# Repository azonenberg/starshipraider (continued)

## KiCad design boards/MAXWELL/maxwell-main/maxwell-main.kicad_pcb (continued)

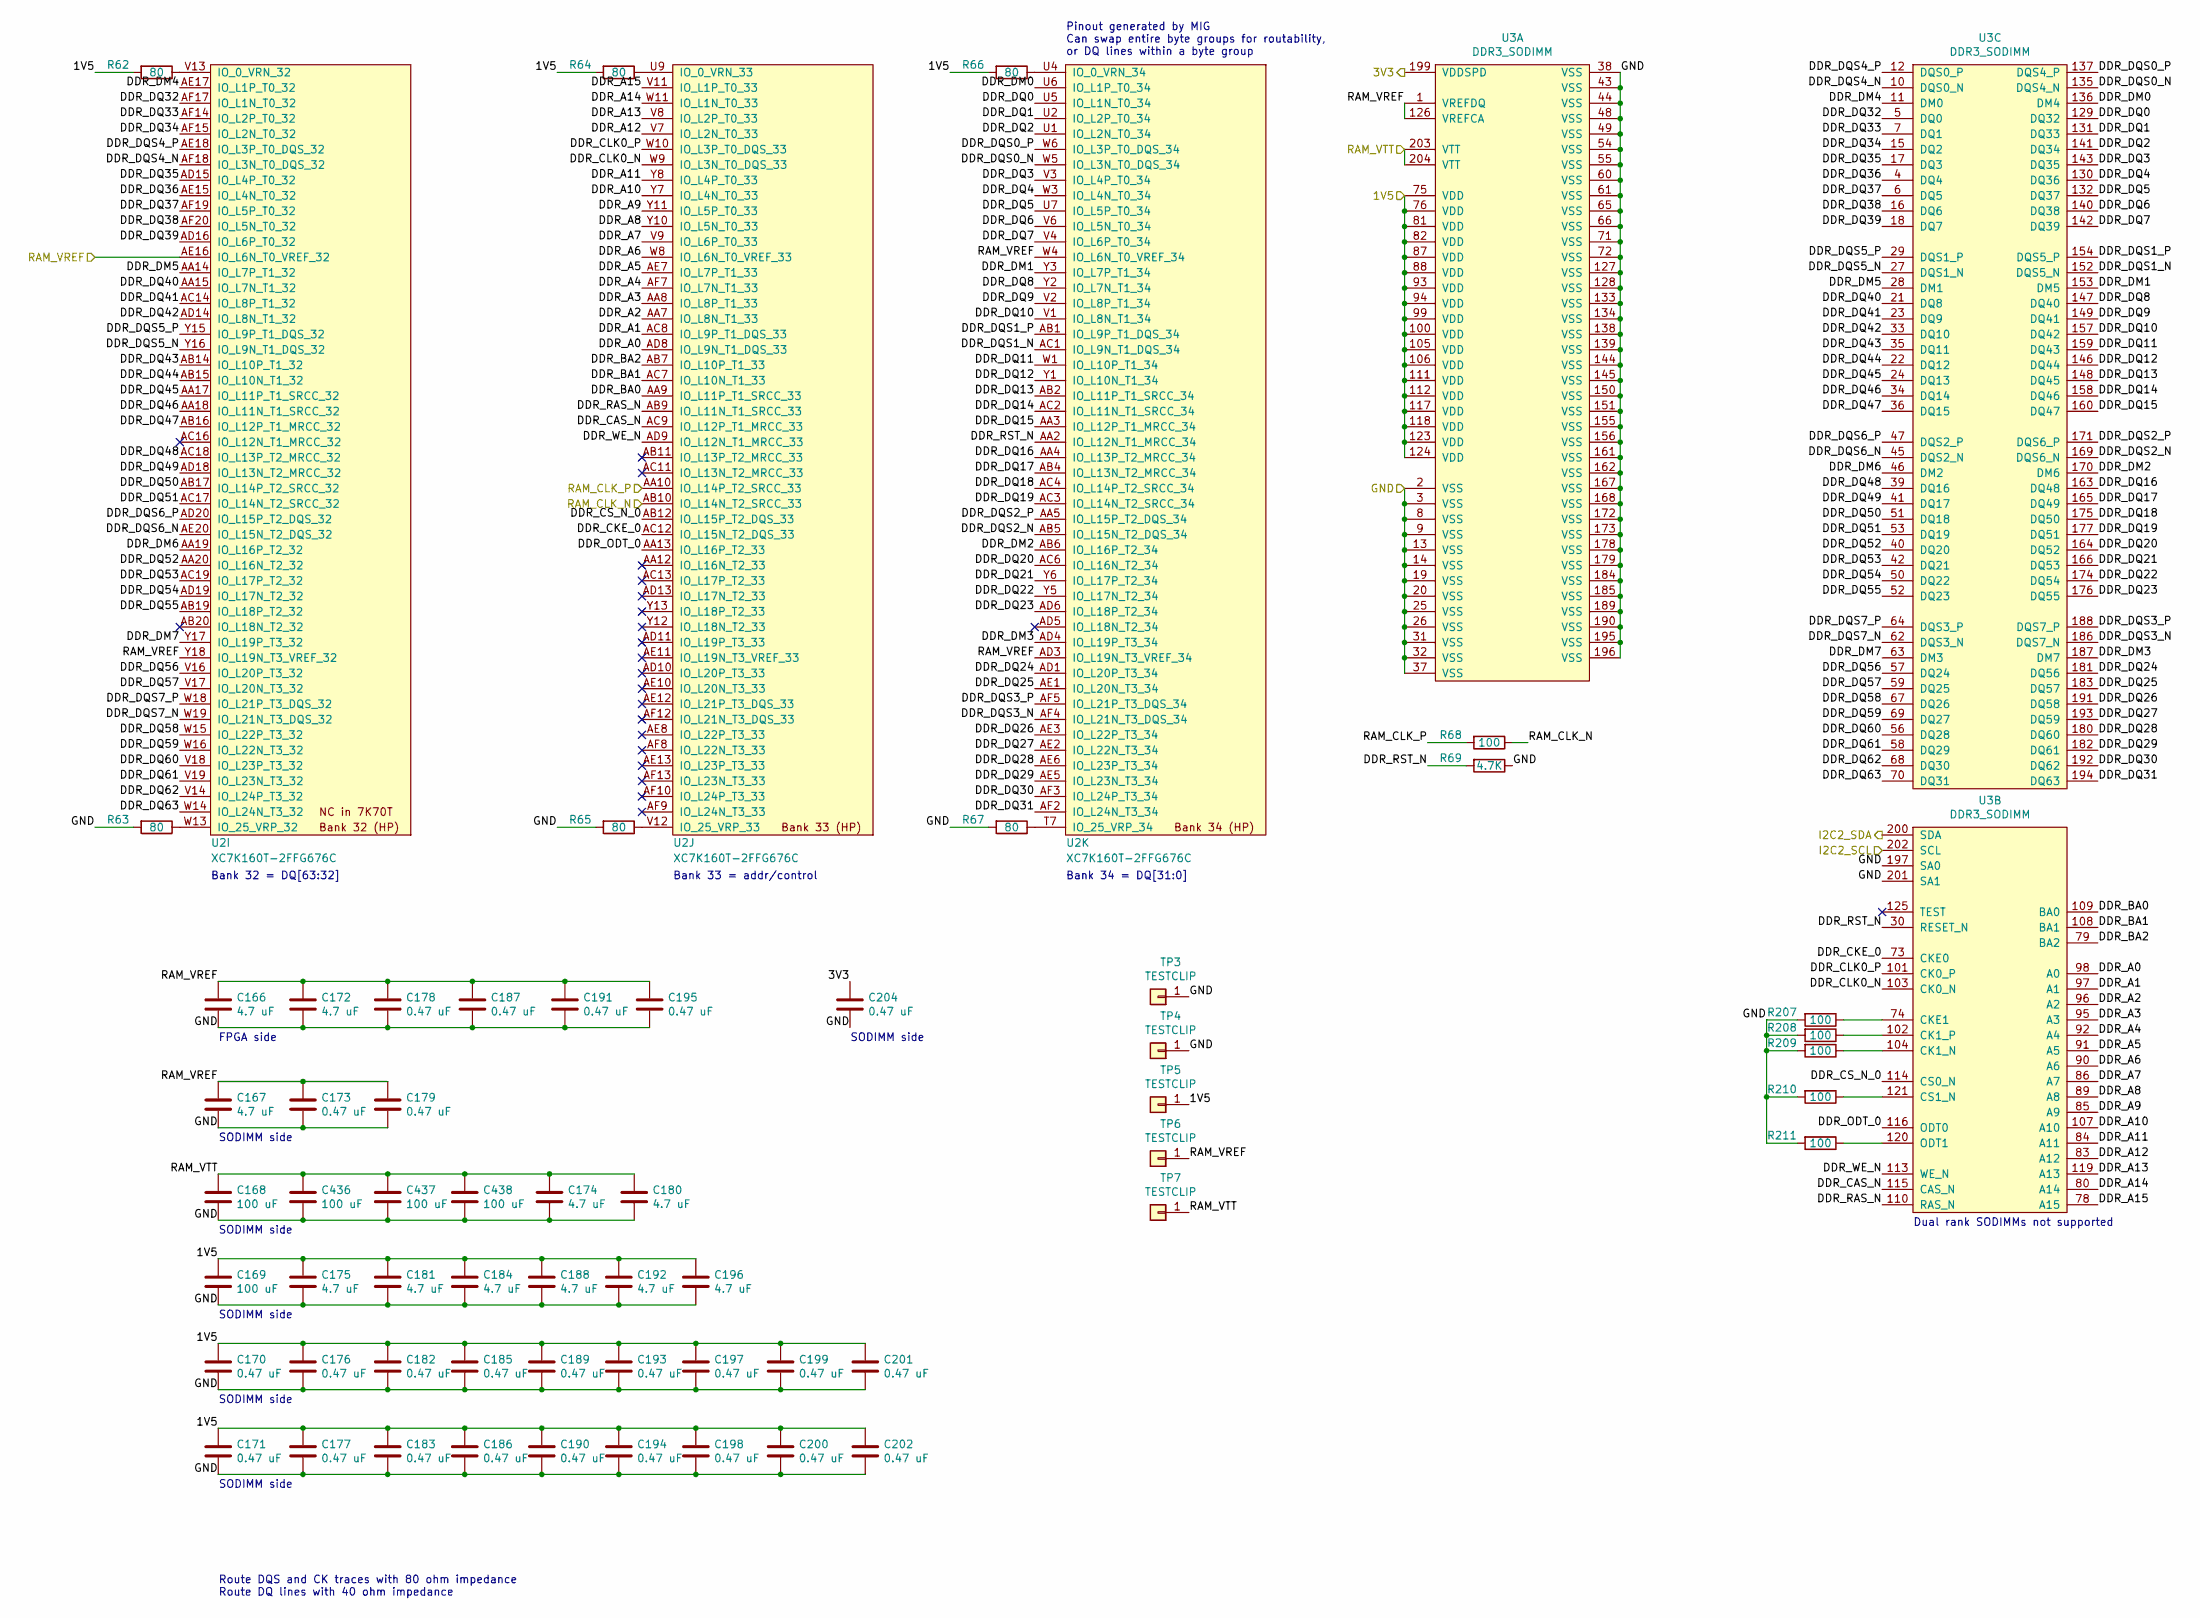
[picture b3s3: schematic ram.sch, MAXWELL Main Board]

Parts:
C166, C167, C172, C174, C175, C180, C181, C184, C188, C192, C196: 4.7 uF; EIA_0603_CAP_NOSILK
C168, C169, C436, C437, C438: 100 uF; EIA_1210_CAP_NOSILK
C170, C171, C173, C176, C177, C178, C179, C182, C183, C185, C186, C187, C189, C190, C191, C193, C194, C195, C197, C198, C199, C200, C201, C202, C204: 0.47 uF; EIA_0402_CAP_NOSILK
R62, R63, R64, R65, R66, R67: 80; EIA_0402_RES_NOSILK
R68, R207, R208, R209, R210, R211: 100; EIA_0402_RES_NOSILK
R69: 4.7K; EIA_0402_RES_NOSILK
TP3, TP4, TP5, TP6, TP7: TESTCLIP; TESTPOINT_SMT_KEYSTONE_5016
U2: XC7K160T-2FFG676C; BGA_676_27x27_FULLARRAY_1MM_FFG676
U3: DDR3_SODIMM; CONN_SODIMM_DDR3_TE_2013289-1

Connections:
/1V5: C169.1, C170.1, C171.1, C175.1, C176.1, C177.1, C181.1, C182.1, C183.1, C184.1, C185.1, C186.1, C188.1, C189.1, C190.1, C192.1, C193.1, C194.1, C196.1, C197.1, C198.1, C199.1, C200.1, C201.1, C202.1, R62.2, R64.2, R66.2, TP5.1, U3.75 (VDD), U3.76 (VDD), U3.81 (VDD), U3.82 (VDD), U3.87 (VDD), U3.88 (VDD), U3.93 (VDD), U3.94 (VDD), U3.99 (VDD), U3.100 (VDD), U3.105 (VDD), U3.106 (VDD), U3.111 (VDD), U3.112 (VDD), U3.117 (VDD), U3.118 (VDD), U3.123 (VDD), U3.124 (VDD); also elsewhere on the board
/3V3_SB: C204.1, U3.199 (VDDSPD); also elsewhere on the board
/Clocking/RAM_CLK_N: R68.1, U2.AB10 (IO_L14N_T2_SRCC_33); also elsewhere on the board
/Clocking/RAM_CLK_P: R68.2, U2.AA10 (IO_L14P_T2_SRCC_33); also elsewhere on the board
/GND: C166.2, C167.2, C168.2, C169.2, C170.2, C171.2, C172.2, C173.2, C174.2, C175.2, C176.2, C177.2, C178.2, C179.2, C180.2, C181.2, C182.2, C183.2, C184.2, C185.2, C186.2, C187.2, C188.2, C189.2, C190.2, C191.2, C192.2, C193.2, C194.2, C195.2, C196.2, C197.2, C198.2, C199.2, C200.2, C201.2, C202.2, C204.2, C436.2, C437.2, C438.2, R63.2, R65.2, R67.2, R69.1, R207.2, R208.2, R209.2, R210.2, R211.2, TP3.1, TP4.1, U3.2 (VSS), U3.3 (VSS), U3.8 (VSS), U3.9 (VSS), U3.13 (VSS), U3.14 (VSS), U3.19 (VSS), U3.20 (VSS), U3.25 (VSS), U3.26 (VSS), U3.31 (VSS), U3.32 (VSS), U3.37 (VSS), U3.38 (VSS), U3.43 (VSS), U3.44 (VSS), U3.48 (VSS), U3.49 (VSS), U3.54 (VSS), U3.55 (VSS), U3.60 (VSS), U3.61 (VSS), U3.65 (VSS), U3.66 (VSS), U3.71 (VSS), U3.72 (VSS), U3.127 (VSS), U3.128 (VSS), U3.133 (VSS), U3.134 (VSS), U3.138 (VSS), U3.139 (VSS), U3.144 (VSS), U3.145 (VSS), U3.150 (VSS), U3.151 (VSS), U3.155 (VSS), U3.156 (VSS), U3.161 (VSS), U3.162 (VSS), U3.167 (VSS), U3.168 (VSS), U3.172 (VSS), U3.173 (VSS), U3.178 (VSS), U3.179 (VSS), U3.184 (VSS), U3.185 (VSS), U3.189 (VSS), U3.190 (VSS), U3.195 (VSS), U3.196 (VSS), U3.197 (SA0), U3.201 (SA1); also elsewhere on the board
/I2C2_SCL: U3.202 (SCL); also elsewhere on the board
/I2C2_SDA: U3.200 (SDA); also elsewhere on the board
/RAM/DDR_A0: U2.AD8 (IO_L9N_T1_DQS_33), U3.98 (A0)
/RAM/DDR_A1: U2.AC8 (IO_L9P_T1_DQS_33), U3.97 (A1)
/RAM/DDR_A2: U2.AA7 (IO_L8N_T1_33), U3.96 (A2)
/RAM/DDR_A3: U2.AA8 (IO_L8P_T1_33), U3.95 (A3)
/RAM/DDR_A4: U2.AF7 (IO_L7N_T1_33), U3.92 (A4)
/RAM/DDR_A5: U2.AE7 (IO_L7P_T1_33), U3.91 (A5)
/RAM/DDR_A6: U2.W8 (IO_L6N_T0_VREF_33), U3.90 (A6)
/RAM/DDR_A7: U2.V9 (IO_L6P_T0_33), U3.86 (A7)
/RAM/DDR_A8: U2.Y10 (IO_L5N_T0_33), U3.89 (A8)
/RAM/DDR_A9: U2.Y11 (IO_L5P_T0_33), U3.85 (A9)
/RAM/DDR_A10: U2.Y7 (IO_L4N_T0_33), U3.107 (A10)
/RAM/DDR_A11: U2.Y8 (IO_L4P_T0_33), U3.84 (A11)
/RAM/DDR_A12: U2.V7 (IO_L2N_T0_33), U3.83 (A12)
/RAM/DDR_A13: U2.V8 (IO_L2P_T0_33), U3.119 (A13)
/RAM/DDR_A14: U2.W11 (IO_L1N_T0_33), U3.80 (A14)
/RAM/DDR_A15: U2.V11 (IO_L1P_T0_33), U3.78 (A15)
/RAM/DDR_BA0: U2.AA9 (IO_L11P_T1_SRCC_33), U3.109 (BA0)
/RAM/DDR_BA1: U2.AC7 (IO_L10N_T1_33), U3.108 (BA1)
/RAM/DDR_BA2: U2.AB7 (IO_L10P_T1_33), U3.79 (BA2)
/RAM/DDR_CAS_N: U2.AC9 (IO_L12P_T1_MRCC_33), U3.115 (CAS_N)
/RAM/DDR_CKE_0: U2.AC12 (IO_L15N_T2_DQS_33), U3.73 (CKE0)
/RAM/DDR_CLK0_N: U2.W9 (IO_L3N_T0_DQS_33), U3.103 (CK0_N)
/RAM/DDR_CLK0_P: U2.W10 (IO_L3P_T0_DQS_33), U3.101 (CK0_P)
/RAM/DDR_CS_N_0: U2.AB12 (IO_L15P_T2_DQS_33), U3.114 (CS0_N)
/RAM/DDR_DM0: U2.U6 (IO_L1P_T0_34), U3.136 (DM4)
/RAM/DDR_DM1: U2.Y3 (IO_L7P_T1_34), U3.153 (DM5)
/RAM/DDR_DM2: U2.AB6 (IO_L16P_T2_34), U3.170 (DM6)
/RAM/DDR_DM3: U2.AD4 (IO_L19P_T3_34), U3.187 (DM7)
/RAM/DDR_DM4: U2.AE17 (IO_L1P_T0_32), U3.11 (DM0)
/RAM/DDR_DM5: U2.AA14 (IO_L7P_T1_32), U3.28 (DM1)
/RAM/DDR_DM6: U2.AA19 (IO_L16P_T2_32), U3.46 (DM2)
/RAM/DDR_DM7: U2.Y17 (IO_L19P_T3_32), U3.63 (DM3)
/RAM/DDR_DQ0: U2.U5 (IO_L1N_T0_34), U3.129 (DQ32)
/RAM/DDR_DQ1: U2.U2 (IO_L2P_T0_34), U3.131 (DQ33)
/RAM/DDR_DQ2: U2.U1 (IO_L2N_T0_34), U3.141 (DQ34)
/RAM/DDR_DQ3: U2.V3 (IO_L4P_T0_34), U3.143 (DQ35)
/RAM/DDR_DQ4: U2.W3 (IO_L4N_T0_34), U3.130 (DQ36)
/RAM/DDR_DQ5: U2.U7 (IO_L5P_T0_34), U3.132 (DQ37)
/RAM/DDR_DQ6: U2.V6 (IO_L5N_T0_34), U3.140 (DQ38)
/RAM/DDR_DQ7: U2.V4 (IO_L6P_T0_34), U3.142 (DQ39)
/RAM/DDR_DQ8: U2.Y2 (IO_L7N_T1_34), U3.147 (DQ40)
/RAM/DDR_DQ9: U2.V2 (IO_L8P_T1_34), U3.149 (DQ41)
/RAM/DDR_DQ10: U2.V1 (IO_L8N_T1_34), U3.157 (DQ42)
/RAM/DDR_DQ11: U2.W1 (IO_L10P_T1_34), U3.159 (DQ43)
/RAM/DDR_DQ12: U2.Y1 (IO_L10N_T1_34), U3.146 (DQ44)
/RAM/DDR_DQ13: U2.AB2 (IO_L11P_T1_SRCC_34), U3.148 (DQ45)
/RAM/DDR_DQ14: U2.AC2 (IO_L11N_T1_SRCC_34), U3.158 (DQ46)
/RAM/DDR_DQ15: U2.AA3 (IO_L12P_T1_MRCC_34), U3.160 (DQ47)
/RAM/DDR_DQ16: U2.AA4 (IO_L13P_T2_MRCC_34), U3.163 (DQ48)
/RAM/DDR_DQ17: U2.AB4 (IO_L13N_T2_MRCC_34), U3.165 (DQ49)
/RAM/DDR_DQ18: U2.AC4 (IO_L14P_T2_SRCC_34), U3.175 (DQ50)
/RAM/DDR_DQ19: U2.AC3 (IO_L14N_T2_SRCC_34), U3.177 (DQ51)
/RAM/DDR_DQ20: U2.AC6 (IO_L16N_T2_34), U3.164 (DQ52)
/RAM/DDR_DQ21: U2.Y6 (IO_L17P_T2_34), U3.166 (DQ53)
/RAM/DDR_DQ22: U2.Y5 (IO_L17N_T2_34), U3.174 (DQ54)
/RAM/DDR_DQ23: U2.AD6 (IO_L18P_T2_34), U3.176 (DQ55)
/RAM/DDR_DQ24: U2.AD1 (IO_L20P_T3_34), U3.181 (DQ56)
/RAM/DDR_DQ25: U2.AE1 (IO_L20N_T3_34), U3.183 (DQ57)
/RAM/DDR_DQ26: U2.AE3 (IO_L22P_T3_34), U3.191 (DQ58)
/RAM/DDR_DQ27: U2.AE2 (IO_L22N_T3_34), U3.193 (DQ59)
/RAM/DDR_DQ28: U2.AE6 (IO_L23P_T3_34), U3.180 (DQ60)
/RAM/DDR_DQ29: U2.AE5 (IO_L23N_T3_34), U3.182 (DQ61)
/RAM/DDR_DQ30: U2.AF3 (IO_L24P_T3_34), U3.192 (DQ62)
/RAM/DDR_DQ31: U2.AF2 (IO_L24N_T3_34), U3.194 (DQ63)
/RAM/DDR_DQ32: U2.AF17 (IO_L1N_T0_32), U3.5 (DQ0)
/RAM/DDR_DQ33: U2.AF14 (IO_L2P_T0_32), U3.7 (DQ1)
/RAM/DDR_DQ34: U2.AF15 (IO_L2N_T0_32), U3.15 (DQ2)
/RAM/DDR_DQ35: U2.AD15 (IO_L4P_T0_32), U3.17 (DQ3)
/RAM/DDR_DQ36: U2.AE15 (IO_L4N_T0_32), U3.4 (DQ4)
/RAM/DDR_DQ37: U2.AF19 (IO_L5P_T0_32), U3.6 (DQ5)
/RAM/DDR_DQ38: U2.AF20 (IO_L5N_T0_32), U3.16 (DQ6)
/RAM/DDR_DQ39: U2.AD16 (IO_L6P_T0_32), U3.18 (DQ7)
/RAM/DDR_DQ40: U2.AA15 (IO_L7N_T1_32), U3.21 (DQ8)
/RAM/DDR_DQ41: U2.AC14 (IO_L8P_T1_32), U3.23 (DQ9)
/RAM/DDR_DQ42: U2.AD14 (IO_L8N_T1_32), U3.33 (DQ10)
/RAM/DDR_DQ43: U2.AB14 (IO_L10P_T1_32), U3.35 (DQ11)
/RAM/DDR_DQ44: U2.AB15 (IO_L10N_T1_32), U3.22 (DQ12)
/RAM/DDR_DQ45: U2.AA17 (IO_L11P_T1_SRCC_32), U3.24 (DQ13)
/RAM/DDR_DQ46: U2.AA18 (IO_L11N_T1_SRCC_32), U3.34 (DQ14)
/RAM/DDR_DQ47: U2.AB16 (IO_L12P_T1_MRCC_32), U3.36 (DQ15)
/RAM/DDR_DQ48: U2.AC18 (IO_L13P_T2_MRCC_32), U3.39 (DQ16)
/RAM/DDR_DQ49: U2.AD18 (IO_L13N_T2_MRCC_32), U3.41 (DQ17)
/RAM/DDR_DQ50: U2.AB17 (IO_L14P_T2_SRCC_32), U3.51 (DQ18)
/RAM/DDR_DQ51: U2.AC17 (IO_L14N_T2_SRCC_32), U3.53 (DQ19)
/RAM/DDR_DQ52: U2.AA20 (IO_L16N_T2_32), U3.40 (DQ20)
/RAM/DDR_DQ53: U2.AC19 (IO_L17P_T2_32), U3.42 (DQ21)
/RAM/DDR_DQ54: U2.AD19 (IO_L17N_T2_32), U3.50 (DQ22)
/RAM/DDR_DQ55: U2.AB19 (IO_L18P_T2_32), U3.52 (DQ23)
/RAM/DDR_DQ56: U2.V16 (IO_L20P_T3_32), U3.57 (DQ24)
/RAM/DDR_DQ57: U2.V17 (IO_L20N_T3_32), U3.59 (DQ25)
/RAM/DDR_DQ58: U2.W15 (IO_L22P_T3_32), U3.67 (DQ26)
/RAM/DDR_DQ59: U2.W16 (IO_L22N_T3_32), U3.69 (DQ27)
/RAM/DDR_DQ60: U2.V18 (IO_L23P_T3_32), U3.56 (DQ28)
/RAM/DDR_DQ61: U2.V19 (IO_L23N_T3_32), U3.58 (DQ29)
/RAM/DDR_DQ62: U2.V14 (IO_L24P_T3_32), U3.68 (DQ30)
/RAM/DDR_DQ63: U2.W14 (IO_L24N_T3_32), U3.70 (DQ31)
/RAM/DDR_DQS0_N: U2.W5 (IO_L3N_T0_DQS_34), U3.135 (DQS4_N)
/RAM/DDR_DQS0_P: U2.W6 (IO_L3P_T0_DQS_34), U3.137 (DQS4_P)
/RAM/DDR_DQS1_N: U2.AC1 (IO_L9N_T1_DQS_34), U3.152 (DQS5_N)
/RAM/DDR_DQS1_P: U2.AB1 (IO_L9P_T1_DQS_34), U3.154 (DQS5_P)
/RAM/DDR_DQS2_N: U2.AB5 (IO_L15N_T2_DQS_34), U3.169 (DQS6_N)
/RAM/DDR_DQS2_P: U2.AA5 (IO_L15P_T2_DQS_34), U3.171 (DQS6_P)
/RAM/DDR_DQS3_N: U2.AF4 (IO_L21N_T3_DQS_34), U3.186 (DQS7_N)
/RAM/DDR_DQS3_P: U2.AF5 (IO_L21P_T3_DQS_34), U3.188 (DQS7_P)
/RAM/DDR_DQS4_N: U2.AF18 (IO_L3N_T0_DQS_32), U3.10 (DQS0_N)
/RAM/DDR_DQS4_P: U2.AE18 (IO_L3P_T0_DQS_32), U3.12 (DQS0_P)
/RAM/DDR_DQS5_N: U2.Y16 (IO_L9N_T1_DQS_32), U3.27 (DQS1_N)
/RAM/DDR_DQS5_P: U2.Y15 (IO_L9P_T1_DQS_32), U3.29 (DQS1_P)
/RAM/DDR_DQS6_N: U2.AE20 (IO_L15N_T2_DQS_32), U3.45 (DQS2_N)
/RAM/DDR_DQS6_P: U2.AD20 (IO_L15P_T2_DQS_32), U3.47 (DQS2_P)
/RAM/DDR_DQS7_N: U2.W19 (IO_L21N_T3_DQS_32), U3.62 (DQS3_N)
/RAM/DDR_DQS7_P: U2.W18 (IO_L21P_T3_DQS_32), U3.64 (DQS3_P)
/RAM/DDR_ODT_0: U2.AA13 (IO_L16P_T2_33), U3.116 (ODT0)
/RAM/DDR_RAS_N: U2.AB9 (IO_L11N_T1_SRCC_33), U3.110 (RAS_N)
/RAM/DDR_RST_N: R69.2, U2.AA2 (IO_L12N_T1_MRCC_34), U3.30 (RESET_N)
/RAM/DDR_WE_N: U2.AD9 (IO_L12N_T1_MRCC_33), U3.113 (WE_N)
/RAM_VREF: C166.1, C167.1, C172.1, C173.1, C178.1, C179.1, C187.1, C191.1, C195.1, TP6.1, U2.AD3 (IO_L19N_T3_VREF_34), U2.AE16 (IO_L6N_T0_VREF_32), U2.W4 (IO_L6N_T0_VREF_34), U2.Y18 (IO_L19N_T3_VREF_32), U3.1 (VREFDQ), U3.126 (VREFCA); also elsewhere on the board
/RAM_VTT: C168.1, C174.1, C180.1, C436.1, C437.1, C438.1, TP7.1, U3.203 (VTT), U3.204 (VTT); also elsewhere on the board
unnamed: R62.1, U2.V13 (IO_0_VRN_32)
unnamed: R63.1, U2.W13 (IO_25_VRP_32)
unnamed: R64.1, U2.U9 (IO_0_VRN_33)
unnamed: R65.1, U2.V12 (IO_25_VRP_33)
unnamed: R66.1, U2.U4 (IO_0_VRN_34)
unnamed: R67.1, U2.T7 (IO_25_VRP_34)
unnamed: R207.1, U3.74 (CKE1)
unnamed: R208.1, U3.102 (CK1_P)
unnamed: R209.1, U3.104 (CK1_N)
unnamed: R210.1, U3.121 (CS1_N)
unnamed: R211.1, U3.120 (ODT1)

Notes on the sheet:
Bank 33 = addr/control
Bank 34 = DQ[31:0]
Bank 32 = DQ[63:32]
Pinout generated by MIG Can swap entire byte groups for routability, or DQ lines within a byte group
Route DQS and CK traces with 80 ohm impedance Route DQ lines with 40 ohm impedance
Dual rank SODIMMs not supported
FPGA side
SODIMM side

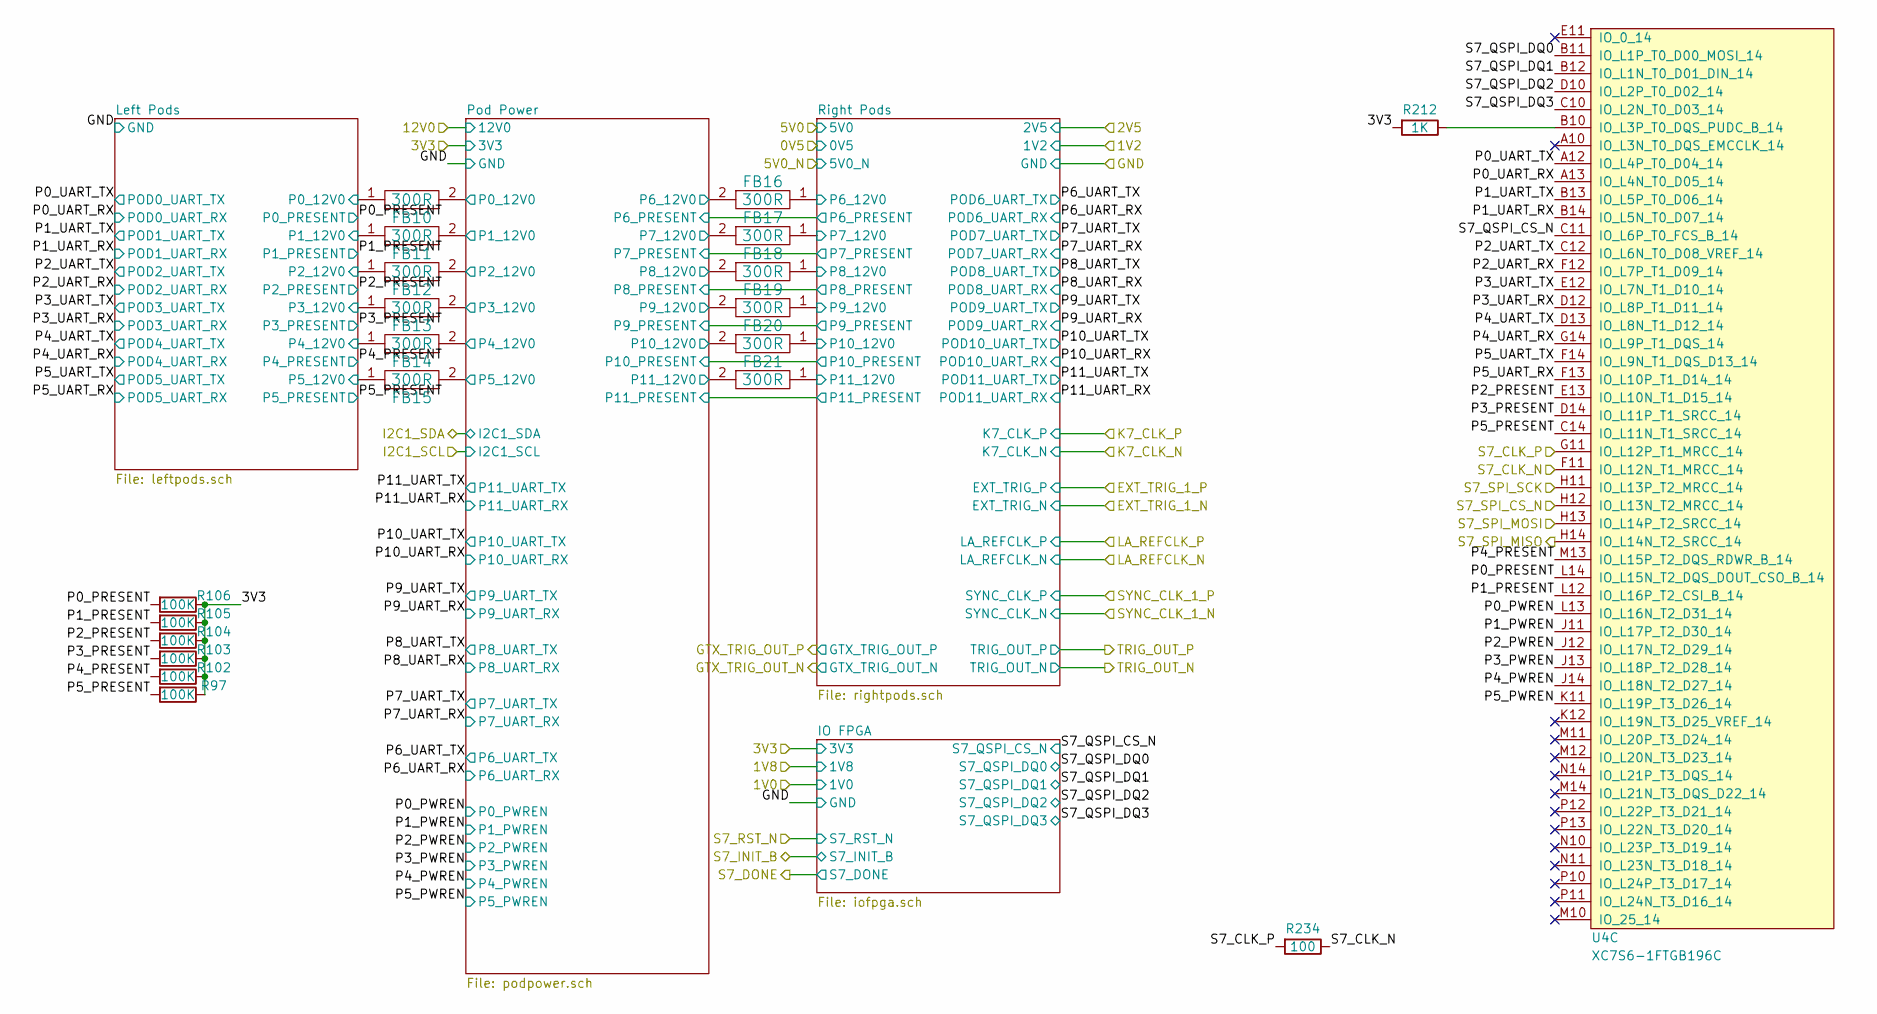
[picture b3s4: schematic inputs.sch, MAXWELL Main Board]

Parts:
FB10, FB11, FB12, FB13, FB14, FB15, FB16, FB17, FB18, FB19, FB20, FB21: 300R; EIA_2220_INDUCTOR
R97, R102, R103, R104, R105, R106: 100K; EIA_0402_RES_NOSILK
R212: 1K; EIA_0402_RES_NOSILK
R234: 100; EIA_0402_RES_NOSILK
U4: XC7S6-1FTGB196C; BGA_196_15x15_FULLARRAY_1MM_FTGB196

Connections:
/3V3: R97.1, R102.1, R103.1, R104.1, R105.1, R106.1, R212.2; also elsewhere on the board
/Clocking/S7_CLK_N: R234.1, U4.F11 (IO_L12N_T1_MRCC_14); also elsewhere on the board
/Clocking/S7_CLK_P: R234.2, U4.G11 (IO_L12P_T1_MRCC_14); also elsewhere on the board
/Inputs/Left Pods/P0_12V0: FB10.1; also elsewhere on the board
/Inputs/Left Pods/P1_12V0: FB11.1; also elsewhere on the board
/Inputs/Left Pods/P2_12V0: FB12.1; also elsewhere on the board
/Inputs/Left Pods/P3_12V0: FB13.1; also elsewhere on the board
/Inputs/Left Pods/P4_12V0: FB14.1; also elsewhere on the board
/Inputs/Left Pods/P5_12V0: FB15.1; also elsewhere on the board
/Inputs/P0_PRESENT: R106.2, U4.L14 (IO_L15N_T2_DQS_DOUT_CSO_B_14); also elsewhere on the board
/Inputs/P0_PWREN: U4.L13 (IO_L16N_T2_D31_14); also elsewhere on the board
/Inputs/P0_UART_RX: U4.A13 (IO_L4N_T0_D05_14); also elsewhere on the board
/Inputs/P0_UART_TX: U4.A12 (IO_L4P_T0_D04_14); also elsewhere on the board
/Inputs/P1_PRESENT: R105.2, U4.L12 (IO_L16P_T2_CSI_B_14); also elsewhere on the board
/Inputs/P1_PWREN: U4.J11 (IO_L17P_T2_D30_14); also elsewhere on the board
/Inputs/P1_UART_RX: U4.B14 (IO_L5N_T0_D07_14); also elsewhere on the board
/Inputs/P1_UART_TX: U4.B13 (IO_L5P_T0_D06_14); also elsewhere on the board
/Inputs/P2_PRESENT: R104.2, U4.E13 (IO_L10N_T1_D15_14); also elsewhere on the board
/Inputs/P2_PWREN: U4.J12 (IO_L17N_T2_D29_14); also elsewhere on the board
/Inputs/P2_UART_RX: U4.F12 (IO_L7P_T1_D09_14); also elsewhere on the board
/Inputs/P2_UART_TX: U4.C12 (IO_L6N_T0_D08_VREF_14); also elsewhere on the board
/Inputs/P3_PRESENT: R103.2, U4.D14 (IO_L11P_T1_SRCC_14); also elsewhere on the board
/Inputs/P3_PWREN: U4.J13 (IO_L18P_T2_D28_14); also elsewhere on the board
/Inputs/P3_UART_RX: U4.D12 (IO_L8P_T1_D11_14); also elsewhere on the board
/Inputs/P3_UART_TX: U4.E12 (IO_L7N_T1_D10_14); also elsewhere on the board
/Inputs/P4_PRESENT: R102.2, U4.M13 (IO_L15P_T2_DQS_RDWR_B_14); also elsewhere on the board
/Inputs/P4_PWREN: U4.J14 (IO_L18N_T2_D27_14); also elsewhere on the board
/Inputs/P4_UART_RX: U4.G14 (IO_L9P_T1_DQS_14); also elsewhere on the board
/Inputs/P4_UART_TX: U4.D13 (IO_L8N_T1_D12_14); also elsewhere on the board
/Inputs/P5_PRESENT: R97.2, U4.C14 (IO_L11N_T1_SRCC_14); also elsewhere on the board
/Inputs/P5_PWREN: U4.K11 (IO_L19P_T3_D26_14); also elsewhere on the board
/Inputs/P5_UART_RX: U4.F13 (IO_L10P_T1_D14_14); also elsewhere on the board
/Inputs/P5_UART_TX: U4.F14 (IO_L9N_T1_DQS_D13_14); also elsewhere on the board
/Inputs/Pod Power/P0_12V0: FB10.2; also elsewhere on the board
/Inputs/Pod Power/P1_12V0: FB11.2; also elsewhere on the board
/Inputs/Pod Power/P2_12V0: FB12.2; also elsewhere on the board
/Inputs/Pod Power/P3_12V0: FB13.2; also elsewhere on the board
/Inputs/Pod Power/P4_12V0: FB14.2; also elsewhere on the board
/Inputs/Pod Power/P5_12V0: FB15.2; also elsewhere on the board
/Inputs/Pod Power/P6_12V0: FB16.2; also elsewhere on the board
/Inputs/Pod Power/P7_12V0: FB17.2; also elsewhere on the board
/Inputs/Pod Power/P8_12V0: FB18.2; also elsewhere on the board
/Inputs/Pod Power/P9_12V0: FB19.2; also elsewhere on the board
/Inputs/Pod Power/P10_12V0: FB20.2; also elsewhere on the board
/Inputs/Pod Power/P11_12V0: FB21.2; also elsewhere on the board
/Inputs/Right Pods/P6_12V0: FB16.1; also elsewhere on the board
/Inputs/Right Pods/P7_12V0: FB17.1; also elsewhere on the board
/Inputs/Right Pods/P8_12V0: FB18.1; also elsewhere on the board
/Inputs/Right Pods/P9_12V0: FB19.1; also elsewhere on the board
/Inputs/Right Pods/P10_12V0: FB20.1; also elsewhere on the board
/Inputs/Right Pods/P11_12V0: FB21.1; also elsewhere on the board
/Inputs/S7_QSPI_CS_N: U4.C11 (IO_L6P_T0_FCS_B_14); also elsewhere on the board
/Inputs/S7_QSPI_DQ0: U4.B11 (IO_L1P_T0_D00_MOSI_14); also elsewhere on the board
/Inputs/S7_QSPI_DQ1: U4.B12 (IO_L1N_T0_D01_DIN_14); also elsewhere on the board
/Inputs/S7_QSPI_DQ2: U4.D10 (IO_L2P_T0_D02_14); also elsewhere on the board
/Inputs/S7_QSPI_DQ3: U4.C10 (IO_L2N_T0_D03_14); also elsewhere on the board
/Inputs/S7_SPI_CS_N: U4.H12 (IO_L13N_T2_MRCC_14); also elsewhere on the board
/Inputs/S7_SPI_MISO: U4.H14 (IO_L14N_T2_SRCC_14); also elsewhere on the board
/Inputs/S7_SPI_MOSI: U4.H13 (IO_L14P_T2_SRCC_14); also elsewhere on the board
/Inputs/S7_SPI_SCK: U4.H11 (IO_L13P_T2_MRCC_14); also elsewhere on the board
unnamed: R212.1, U4.B10 (IO_L3P_T0_DQS_PUDC_B_14)

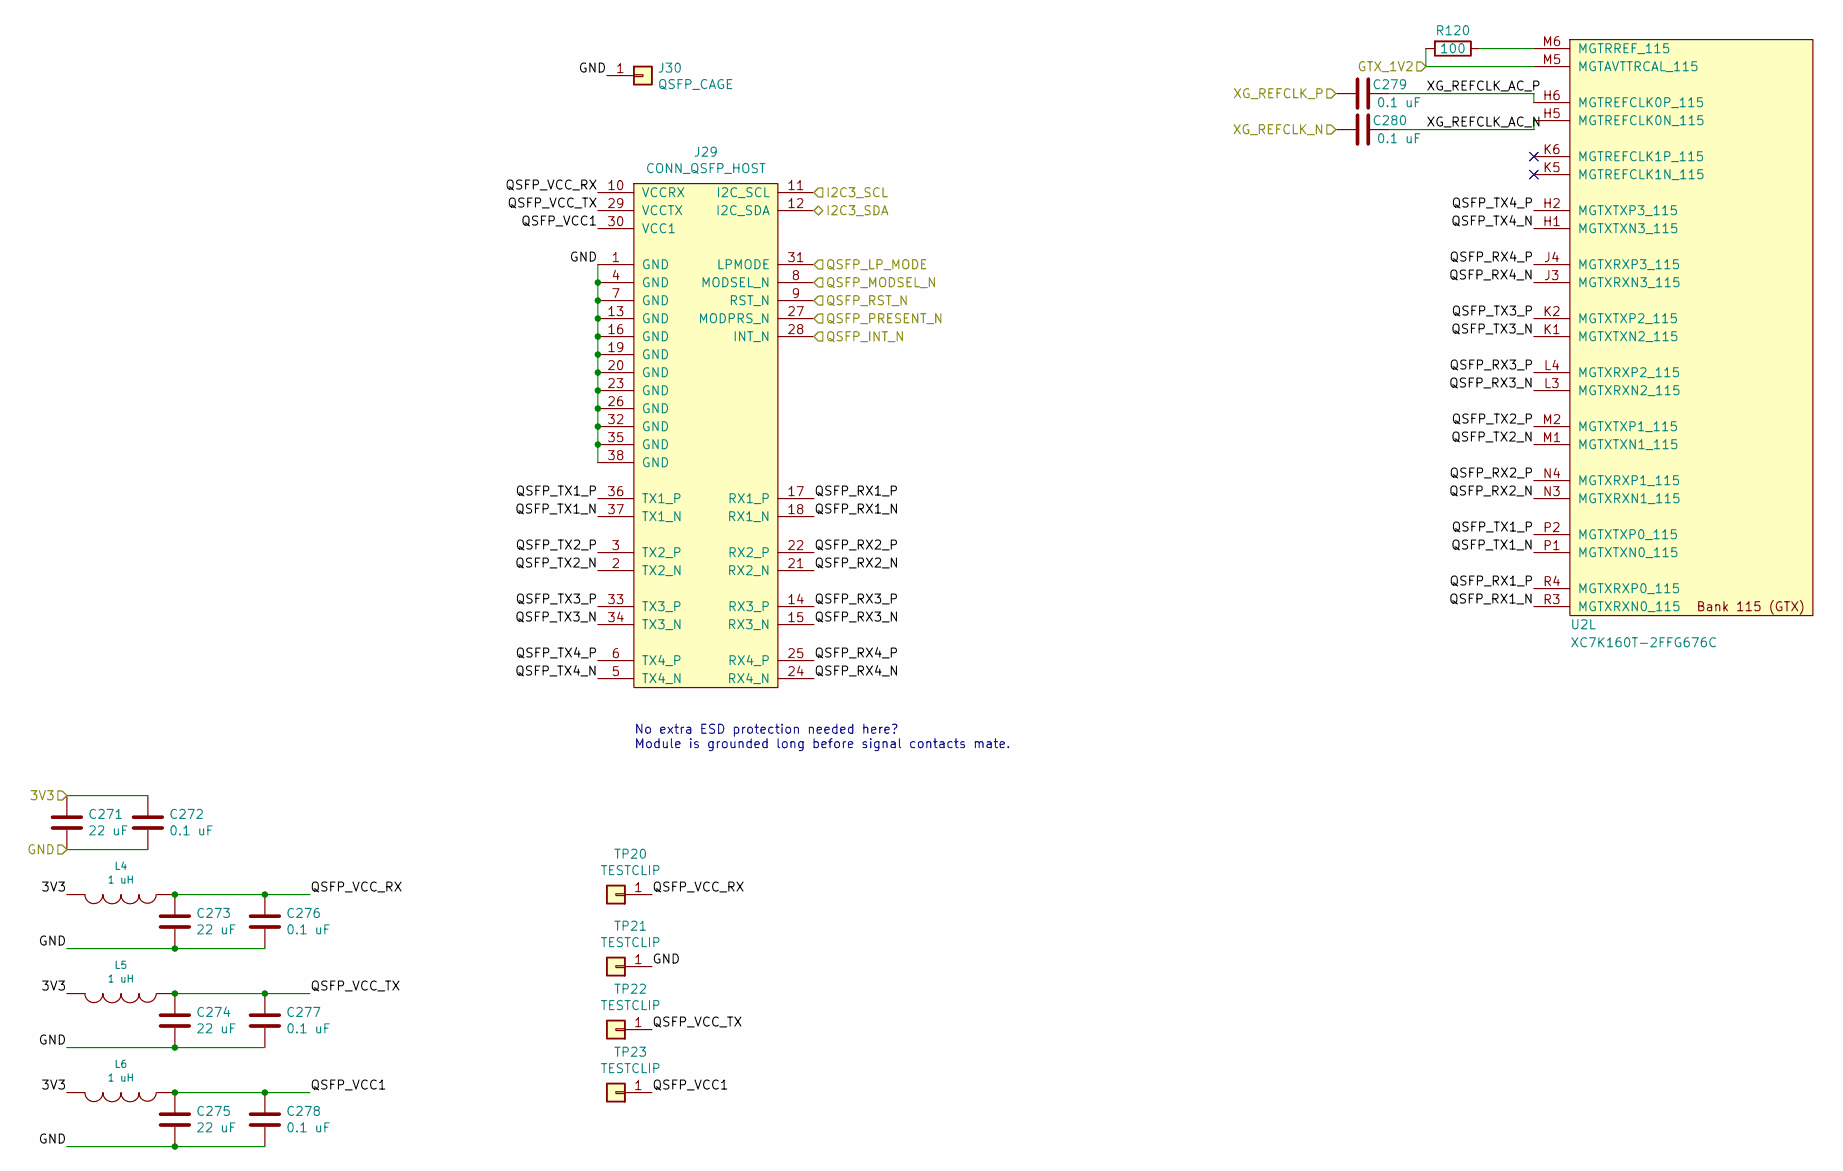
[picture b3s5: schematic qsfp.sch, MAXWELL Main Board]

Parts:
C271, C273, C274, C275: 22 uF; EIA_1210_CAP_NOSILK
C272, C276, C277, C278, C279, C280: 0.1 uF; EIA_0402_CAP_NOSILK
J29: CONN_QSFP_HOST; CONN_QSFP+_TE_2110819-1
J30: QSFP_CAGE; CONN_QSFP_CAGE_TE_2110487-1
L4, L5, L6: 1 uH; EIA_0805_INDUCTOR_NOSILK
R120: 100; EIA_0402_RES_NOSILK
TP20, TP21, TP22, TP23: TESTCLIP; TESTPOINT_SMT_KEYSTONE_5016
U2: XC7K160T-2FFG676C; BGA_676_27x27_FULLARRAY_1MM_FFG676

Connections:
/3V3: C271.1, C272.1, L4.2, L5.2, L6.2; also elsewhere on the board
/Clocking/XG_REFCLK_N: C280.2; also elsewhere on the board
/Clocking/XG_REFCLK_P: C279.2; also elsewhere on the board
/GND: C271.2, C272.2, C273.2, C274.2, C275.2, C276.2, C277.2, C278.2, J29.1 (GND), J29.4 (GND), J29.7 (GND), J29.13 (GND), J29.16 (GND), J29.19 (GND), J29.20 (GND), J29.23 (GND), J29.26 (GND), J29.32 (GND), J29.35 (GND), J29.38 (GND), J30.1, TP21.1; also elsewhere on the board
/GTX_1V2: R120.2, U2.M5 (MGTAVTTRCAL_115); also elsewhere on the board
/I2C3_SCL: J29.11 (I2C_SCL); also elsewhere on the board
/I2C3_SDA: J29.12 (I2C_SDA); also elsewhere on the board
/QSFP+/QSFP_RX1_N: J29.18 (RX1_N), U2.R3 (MGTXRXN0_115)
/QSFP+/QSFP_RX1_P: J29.17 (RX1_P), U2.R4 (MGTXRXP0_115)
/QSFP+/QSFP_RX2_N: J29.21 (RX2_N), U2.N3 (MGTXRXN1_115)
/QSFP+/QSFP_RX2_P: J29.22 (RX2_P), U2.N4 (MGTXRXP1_115)
/QSFP+/QSFP_RX3_N: J29.15 (RX3_N), U2.L3 (MGTXRXN2_115)
/QSFP+/QSFP_RX3_P: J29.14 (RX3_P), U2.L4 (MGTXRXP2_115)
/QSFP+/QSFP_RX4_N: J29.24 (RX4_N), U2.J3 (MGTXRXN3_115)
/QSFP+/QSFP_RX4_P: J29.25 (RX4_P), U2.J4 (MGTXRXP3_115)
/QSFP+/QSFP_TX1_N: J29.37 (TX1_N), U2.P1 (MGTXTXN0_115)
/QSFP+/QSFP_TX1_P: J29.36 (TX1_P), U2.P2 (MGTXTXP0_115)
/QSFP+/QSFP_TX2_N: J29.2 (TX2_N), U2.M1 (MGTXTXN1_115)
/QSFP+/QSFP_TX2_P: J29.3 (TX2_P), U2.M2 (MGTXTXP1_115)
/QSFP+/QSFP_TX3_N: J29.34 (TX3_N), U2.K1 (MGTXTXN2_115)
/QSFP+/QSFP_TX3_P: J29.33 (TX3_P), U2.K2 (MGTXTXP2_115)
/QSFP+/QSFP_TX4_N: J29.5 (TX4_N), U2.H1 (MGTXTXN3_115)
/QSFP+/QSFP_TX4_P: J29.6 (TX4_P), U2.H2 (MGTXTXP3_115)
/QSFP+/QSFP_VCC1: C275.1, C278.1, J29.30 (VCC1), L6.1, TP23.1
/QSFP+/QSFP_VCC_RX: C273.1, C276.1, J29.10 (VCCRX), L4.1, TP20.1
/QSFP+/QSFP_VCC_TX: C274.1, C277.1, J29.29 (VCCTX), L5.1, TP22.1
/QSFP+/XG_REFCLK_AC_N: C280.1, U2.H5 (MGTREFCLK0N_115)
/QSFP+/XG_REFCLK_AC_P: C279.1, U2.H6 (MGTREFCLK0P_115)
/QSFP_INT_N: J29.28 (INT_N); also elsewhere on the board
/QSFP_LP_MODE: J29.31 (LPMODE); also elsewhere on the board
/QSFP_MODSEL_N: J29.8 (MODSEL_N); also elsewhere on the board
/QSFP_PRESENT_N: J29.27 (MODPRS_N); also elsewhere on the board
/QSFP_RST_N: J29.9 (RST_N); also elsewhere on the board
unnamed: R120.1, U2.M6 (MGTRREF_115)

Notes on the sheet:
No extra ESD protection needed here? Module is grounded long before signal contacts mate.
